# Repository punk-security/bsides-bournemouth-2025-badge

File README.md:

# BSides Bournemouth (2025) Skull badge

This badge uses UV full colour silk, and we ordered them from JLCPCB using EasyEDA. The PCB was built first with AutoCAD EAGLE, then exported.

Lots of things in this repo:

- eagle-files: all the stuff you need to tinker and modify the PCB
- gerber-files.zip: the file you can upload to JLCPCB and order your own badge, as is
- bsides-bournemouth-2025-badge.ino: the arduino code that powers the badge, which you can modify and flash via the SAO connector
- skull.svg: the original vector design for the badge
- skull.png: the silkscreen as ordered

## Bill Of Materials

You can see a parts list on DigiKey [here](https://www.digikey.co.uk/en/mylists/list/Z9CH9C1GM3). This is the list for the BSIDES Cheltenham 2024 badge, but it is the same bits.

Essentially its:

* ATTINY402 microcontroller
* Button - any surface mount button fitting the footprint will work
* CR2032 battery clip x 2 - surface mount not through hole
* Neopixel 5050 addressable LED - Definitely get the right version of these

## Eagle designs and ordering your own badge

We've uploaded the AutoCAD EAGLE schematic and board design!  You will probably have to do some tweaks to get it working as they're not designed to be standalone exports.

We've also uploaded the gerber_files.zip.  Take this to JLCPCB and you can order your own exact copies of the board :)

## Writing and flashing code!

We use [MegaTinyCore](https://github.com/SpenceKonde/megaTinyCore) for the arduino interface for ATTINY4x2 chips.

Dev and flashing is done within the Arduino IDE ( < v2 ) using a jtag2updi interface, as discussed [here](https://github.com/SpenceKonde/AVR-Guidance/blob/master/UPDI/jtag2updi.md)

We use [these little usb sticks](https://amzn.eu/d/c0lx0wG), with a 4.7k resistor soldered between the Tx and Rx lines.  

### Installing MegaTinyCore dependencies

This board package can be installed via the board manager in arduino. The boards manager URL is:

`http://drazzy.com/package_drazzy.com_index.json`

1. File -> Preferences, enter the above URL in "Additional Boards Manager URLs"
2. Tools -> Boards -> Boards Manager...
3. Wait while the list loads (takes longer than one would expect, and refreshes several times).
4. Select "megaTinyCore by Spence Konde" and click "Install". For best results, choose the most recent version.

### Setting up the IDE

1. Open the file **bsides-cheltenham-2024-badge.ino** in arduino
2. Select tools > Board > megaTinyCore > ATtiny412/402/212/202
3. Select tools > Chip > ATtiny402
4. Select tools > Clock > 8Mhz internal *(we get power issues otherwise)*
5. Select tools > Programmer > SerialUPDI SLOW
6. Select tools > Port > ( pick your COM port)

### Flashing firmware
1. Connect the 3v3 pin to 3v on your usb (maybe wedge it in the battery clip)
2. Connect GND to GND
3. Connect UPDI to the RxD port
4. Click Upload button

## How to solder?

Make sure to line up the dot on the attiny402 with the dot on the board.

Make sure to line the corner of the LED with the cutout with the triable on the board

*It's much easier if you hold the component in place with one hand, and then solder one pad. Now you can solder the rest of the pads with one hand*

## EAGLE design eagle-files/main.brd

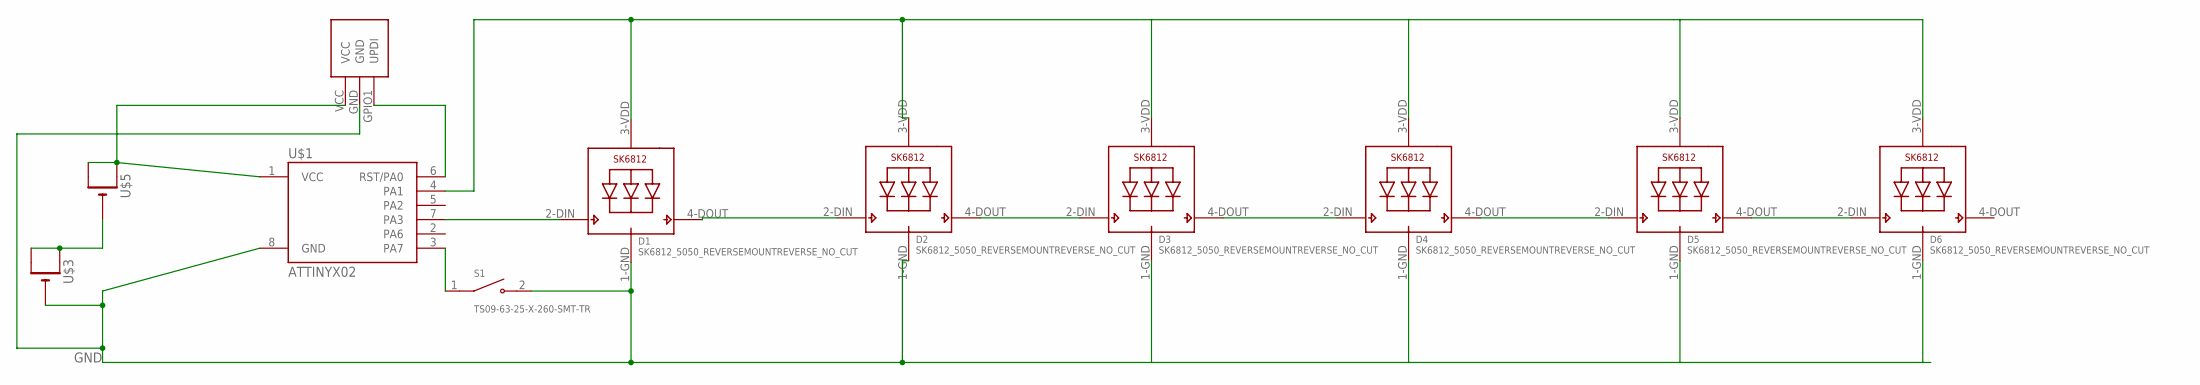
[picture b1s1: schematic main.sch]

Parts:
D1, D2, D3, D4, D5, D6: SK6812_5050_REVERSEMOUNTREVERSE_NO_CUT; SK6812_REVERSE_NO_CUT
S1: TS09-63-25-X-260-SMT-TR; SW_TS09-63-25-X-260-SMT-TR
U$1: ATTINYX02; SOIC08_JEDEC_150MIL
U$2: SAO; SAO_SMD
U$3, U$5: CR2032SMT; CR2032-SMD

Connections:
GND: D1.1-GND (GND), D2.1-GND (GND), D3.1-GND (GND), D4.1-GND (GND), D5.1-GND (GND), D6.1-GND (GND), S1.2, U$1.8 (GND), U$2.GND, U$3.-
unnamed: D1.4-DOUT (DO), D2.2-DIN (DI)
unnamed: D1.2-DIN (DI), U$1.7 (PA3)
unnamed: D3.4-DOUT (DO), D4.2-DIN (DI)
unnamed: D2.4-DOUT (DO), D3.2-DIN (DI)
unnamed: S1.1, U$1.3 (PA7)
unnamed: D4.4-DOUT (DO), D5.2-DIN (DI)
unnamed: D5.4-DOUT (DO), D6.2-DIN (DI)
unnamed: U$3.+$1 (+), U$3.+$2 (+1), U$5.-
unnamed: U$1.6 (RST/PA0), U$2.GPIO1 (UPDI)
VCC1: U$1.1 (VCC), U$2.VCC, U$5.+$1 (+), U$5.+$2 (+1)
VDD1: D1.3-VDD (VDD), D2.3-VDD (VDD), D3.3-VDD (VDD), D4.3-VDD (VDD), D5.3-VDD (VDD), D6.3-VDD (VDD), U$1.4 (PA1)

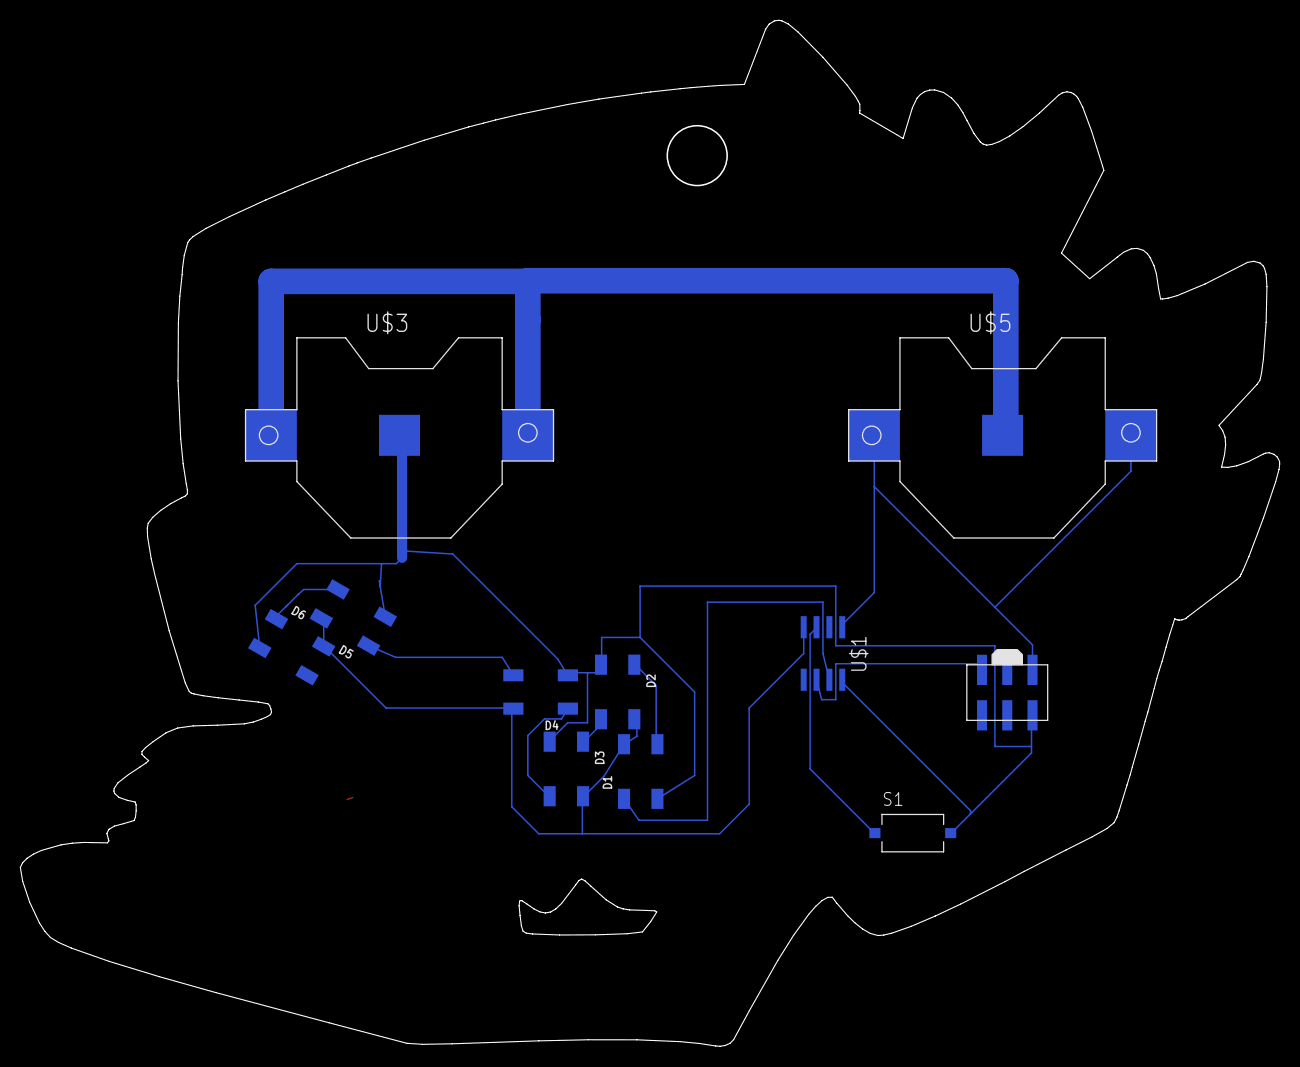
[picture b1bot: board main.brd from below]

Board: 2 copper layers, 124.6 x 101.5 mm, 11 parts (11 on the bottom side), 12 nets.

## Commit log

2025-08-17 go go go!
